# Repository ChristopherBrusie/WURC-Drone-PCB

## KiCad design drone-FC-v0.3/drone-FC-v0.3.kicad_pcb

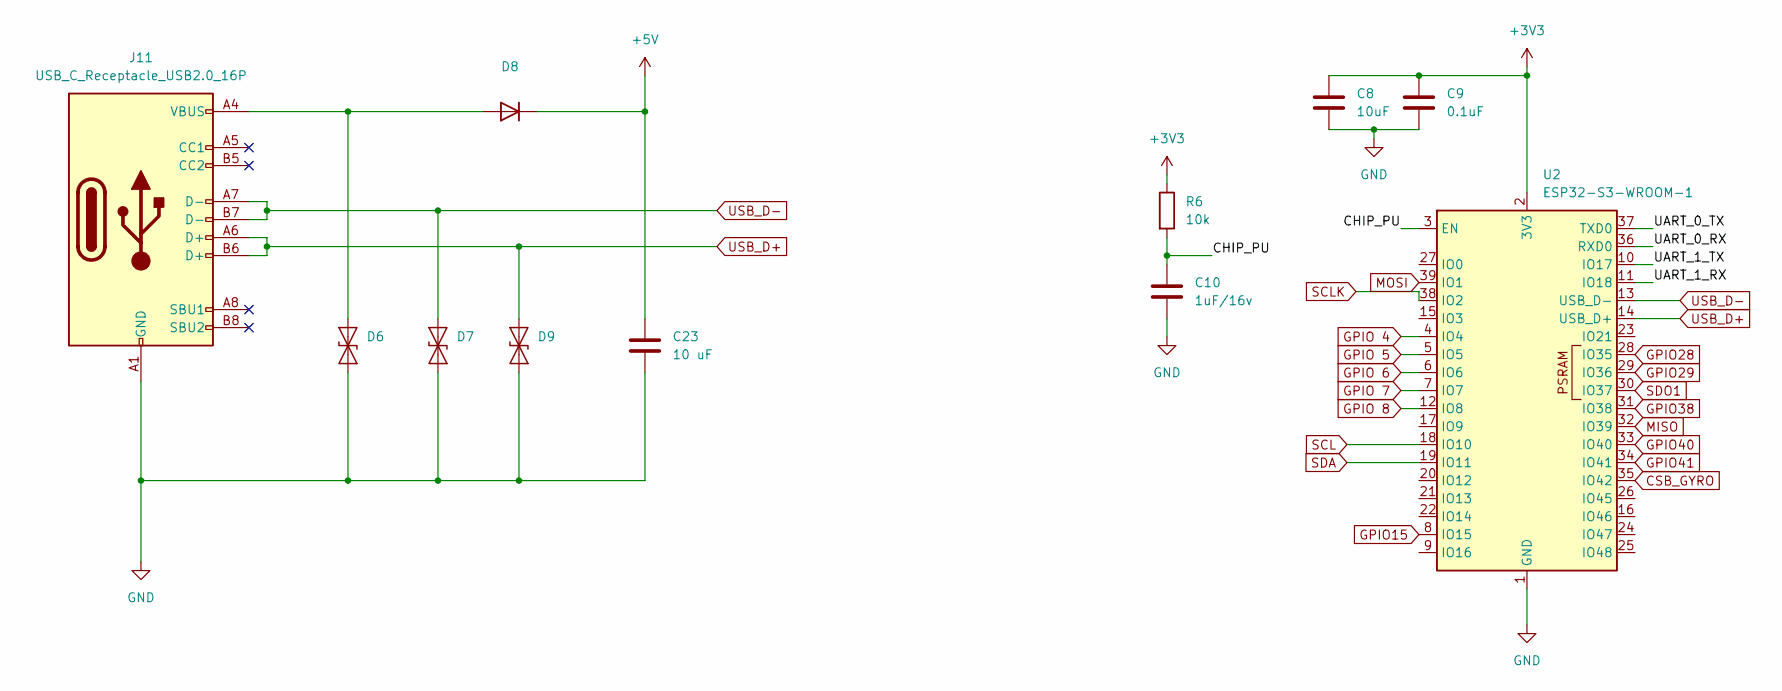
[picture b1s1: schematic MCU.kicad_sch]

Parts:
C8: 10uF; C_0603_1608Metric
C9: 0.1uF; C_0603_1608Metric
C10: 1uF/16v; C_0603_1608Metric
C23: 10 uF; C_0201_0603Metric; LCSC C89632
D6, D7, D9: ESD9B3.3ST5G; D_SOD-923
D8: 1N4148WT; D_SOD-523
J11: USB_C_Receptacle_USB2.0_16P; USB_C_Receptacle_HRO_TYPE-C-31-M-12
R6: 10k; R_0603_1608Metric
U2: ESP32-S3-WROOM-1

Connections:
+3V3: C8.1, C9.1, R6.1, U2.2 (3V3); also elsewhere on the board
+5V: C23.1, D8.1 (K); also elsewhere on the board
/MCU/CHIP_PU: C10.1, R6.2, U2.3 (EN)
/MCU/UART_0_RX: U2.36 (RXD0)
/MCU/UART_0_TX: U2.37 (TXD0)
/MCU/UART_1_RX: U2.11 (IO18)
/MCU/UART_1_TX: U2.10 (IO17)
CSB_GYRO: U2.35 (IO42); also elsewhere on the board
GND: C8.2, C9.2, C10.2, C23.2, D6.1 (A1), D7.1 (A1), D9.1 (A1), J11.A1 (GND), J11.A12 (GND), J11.B1 (GND), J11.B12 (GND), U2.1 (GND), U2.40 (GND), U2.41 (GND); also elsewhere on the board
GPIO15: U2.8 (IO15)
GPIO28: U2.28 (IO35); also elsewhere on the board
GPIO29: U2.29 (IO36); also elsewhere on the board
GPIO38: U2.31 (IO38); also elsewhere on the board
GPIO40: U2.33 (IO40); also elsewhere on the board
GPIO41: U2.34 (IO41); also elsewhere on the board
GPIO 4: U2.4 (IO4); also elsewhere on the board
GPIO 5: U2.5 (IO5); also elsewhere on the board
GPIO 6: U2.6 (IO6); also elsewhere on the board
GPIO 7: U2.7 (IO7); also elsewhere on the board
GPIO 8: U2.12 (IO8); also elsewhere on the board
MISO: U2.32 (IO39); also elsewhere on the board
MOSI: U2.39 (IO1); also elsewhere on the board
unnamed: D6.2 (A2), D8.2 (A), J11.A4 (VBUS), J11.A9 (VBUS), J11.B4 (VBUS), J11.B9 (VBUS)
SCL: U2.18 (IO10); also elsewhere on the board
SCLK: U2.38 (IO2); also elsewhere on the board
SDA: U2.19 (IO11); also elsewhere on the board
SDO1: U2.30 (IO37)
USB_D+: D9.2 (A2), J11.A6 (D+), J11.B6 (D+), U2.14 (USB_D+)
USB_D-: D7.2 (A2), J11.A7 (D-), J11.B7 (D-), U2.13 (USB_D-)

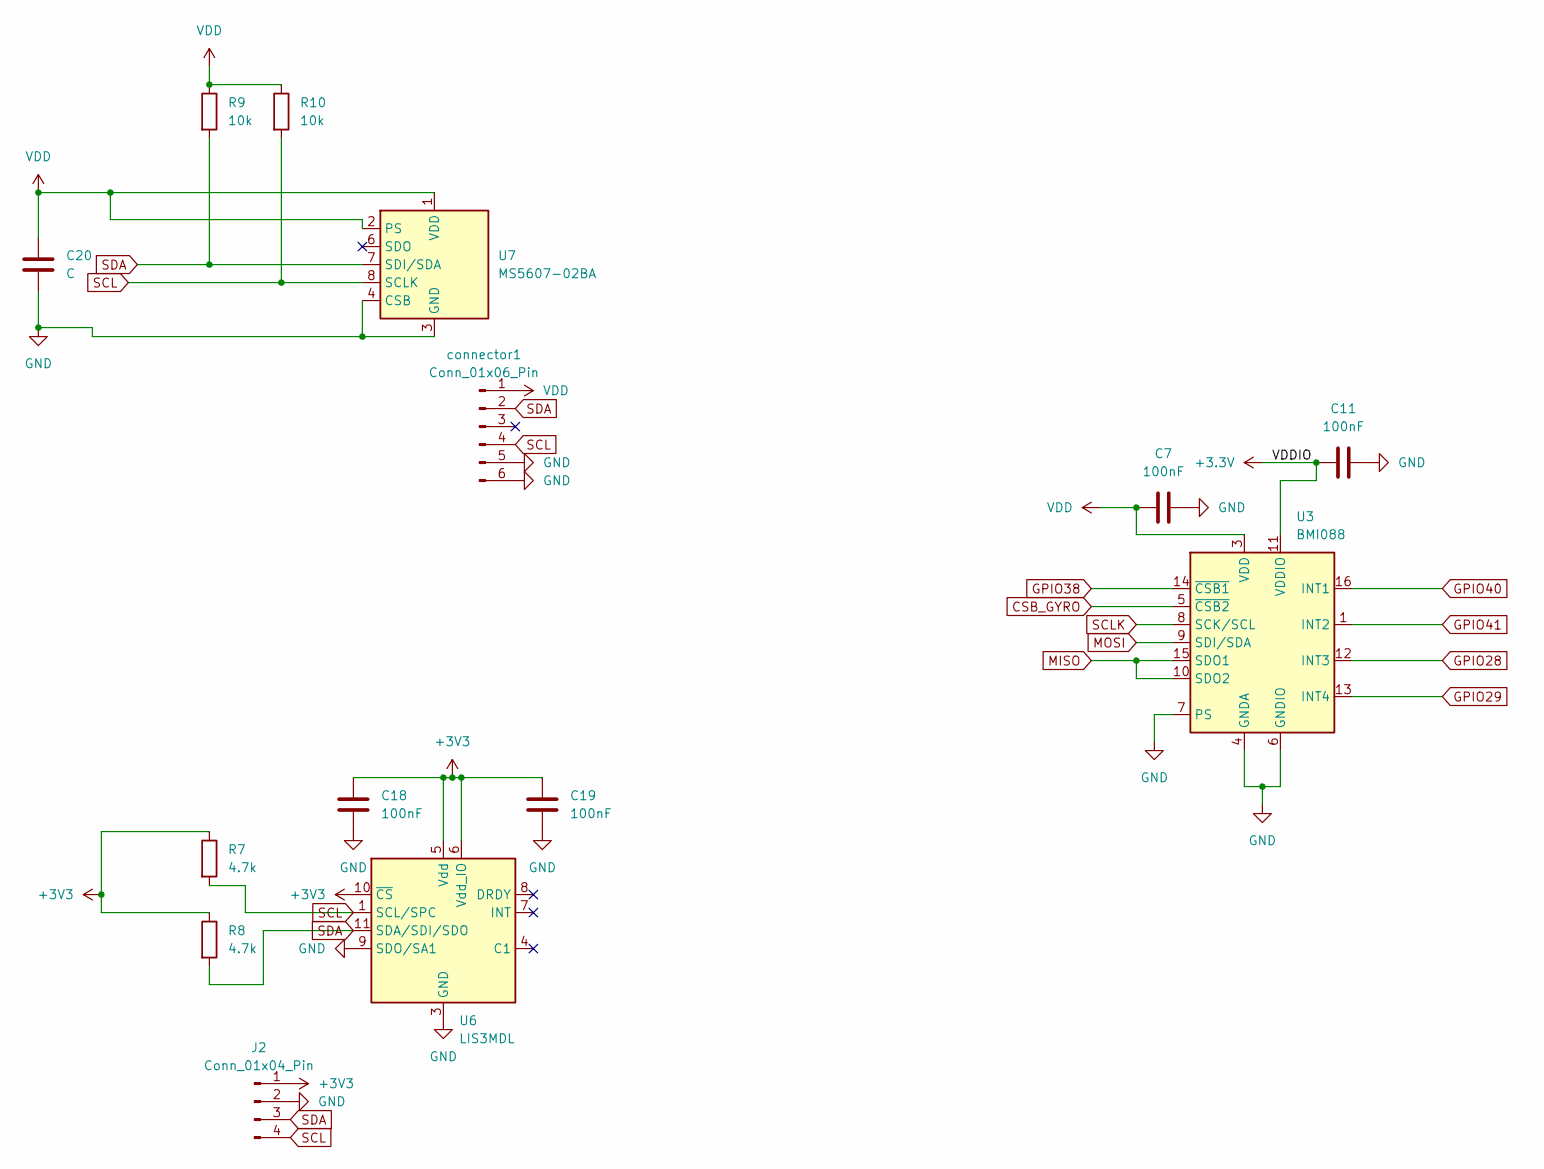
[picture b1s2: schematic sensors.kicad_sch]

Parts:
C7, C11: 100nF; C_0603_1608Metric
C18, C19: 100nF; C_0402_1005Metric
C20: C; C_0201_0603Metric
J2: Conn_01x04_Pin; FanPinHeader_1x04_P2.54mm_Vertical
R7, R8: 4.7k; R_0402_1005Metric
R9, R10: 10k; R_0603_1608Metric_Pad0.98x0.95mm_HandSolder
U3: BMI088; Bosch_LGA-16_4.5x3mm_P0.5mm_LayoutBorder7x1y_ClockwisePinNu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
U6: LIS3MDL; LGA-12_2x2mm_P0.5mm
U7: MS5607-02BA; LGA-8_3x5mm_P1.25mm; lcsc C97627
connector1: Conn_01x06_Pin; PinHeader_1x06_P2.54mm_Vertical

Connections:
+3.3V: C11.1, U3.11 (VDDIO); also elsewhere on the board
+3V3: C18.1, C19.1, J2.1, R7.1, R8.1, U6.5 (Vdd), U6.6 (Vdd_IO), U6.10 (~CS); also elsewhere on the board
CSB_GYRO: U3.5 (~CSB2); also elsewhere on the board
GND: C7.2, C11.2, C18.2, C19.2, C20.2, J2.2, U3.2 (GNDA), U3.4 (GNDA), U3.6 (GNDIO), U3.7 (PS), U6.2 (GND), U6.3 (GND), U6.9 (SDO/SA1), U6.12 (GND), U7.3 (GND), U7.4 (CSB), U7.5 (CSB), connector1.5, connector1.6; also elsewhere on the board
GPIO28: U3.12 (INT3); also elsewhere on the board
GPIO29: U3.13 (INT4); also elsewhere on the board
GPIO38: U3.14 (~CSB1); also elsewhere on the board
GPIO40: U3.16 (INT1); also elsewhere on the board
GPIO41: U3.1 (INT2); also elsewhere on the board
MISO: U3.10 (SDO2), U3.15 (SDO1); also elsewhere on the board
MOSI: U3.9 (SDI/SDA); also elsewhere on the board
SCL: J2.4, R7.2, R10.2, U6.1 (SCL/SPC), U7.8 (SCLK), connector1.4; also elsewhere on the board
SCLK: U3.8 (SCK/SCL); also elsewhere on the board
SDA: J2.3, R8.2, R9.2, U6.11 (SDA/SDI/SDO), U7.7 (SDI/SDA), connector1.2; also elsewhere on the board
VDD: C7.1, C20.1, R9.1, R10.1, U3.3 (VDD), U7.1 (VDD), U7.2 (PS), connector1.1

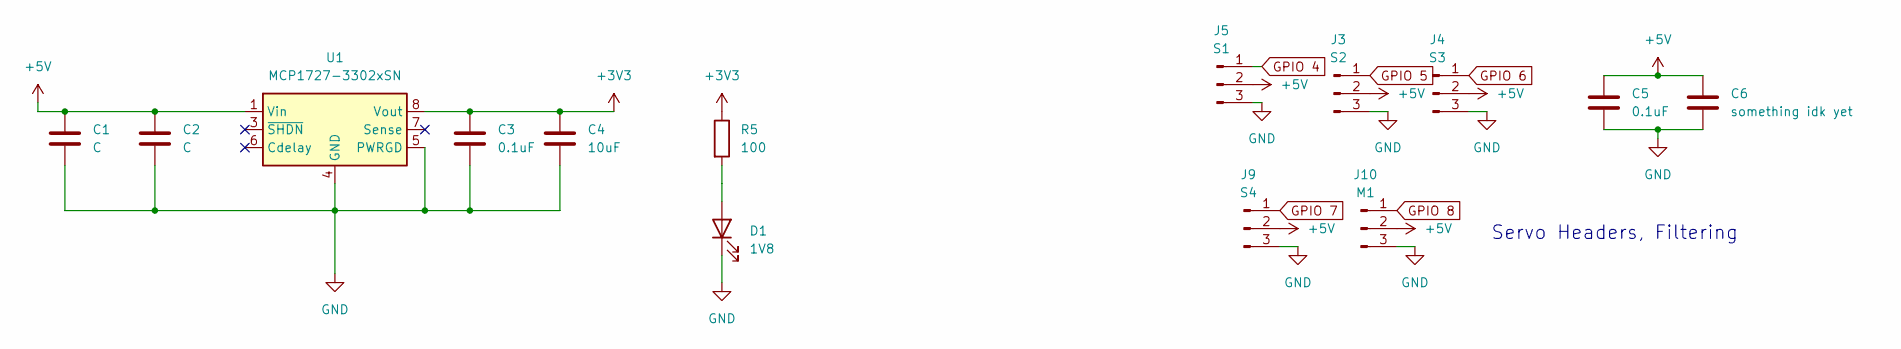
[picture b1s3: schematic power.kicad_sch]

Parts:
C1, C2: C; C_0603_1608Metric
C3: 0.1uF; C_0603_1608Metric
C4: 10uF; C_0603_1608Metric; LCSC C1691
C5: 0.1uF; C_0603_1608Metric; LCSC C91183
C6: something idk yet; C_Radial_D6.3mm_H5.0mm_P2.50mm
D1: 1V8; LED_0603_1608Metric; LCSC C12065
J3: S2; PinHeader_1x03_P2.54mm_Vertical
J4: S3; PinHeader_1x03_P2.54mm_Vertical
J5: S1; PinHeader_1x03_P2.54mm_Vertical
J9: S4; PinHeader_1x03_P2.54mm_Vertical
J10: M1; PinHeader_1x03_P2.54mm_Vertical
R5: 100; R_0603_1608Metric; LCSC C177347
U1: MCP1727-3302xSN; SOIC-8_3.9x4.9mm_P1.27mm

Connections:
+3V3: C3.1, C4.1, R5.1, U1.8 (Vout); also elsewhere on the board
+5V: C1.1, C2.1, C5.1, C6.1, J3.2, J4.2, J5.2, J9.2, J10.2, U1.1 (Vin), U1.2 (Vin); also elsewhere on the board
GND: C1.2, C2.2, C3.2, C4.2, C5.2, C6.2, D1.1 (K), J3.3, J4.3, J5.3, J9.3, J10.3, U1.4 (GND), U1.5 (PWRGD); also elsewhere on the board
GPIO 4: J5.1; also elsewhere on the board
GPIO 5: J3.1; also elsewhere on the board
GPIO 6: J4.1; also elsewhere on the board
GPIO 7: J9.1; also elsewhere on the board
GPIO 8: J10.1; also elsewhere on the board
unnamed: D1.2 (A), R5.2

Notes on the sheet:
Servo Headers, Filtering

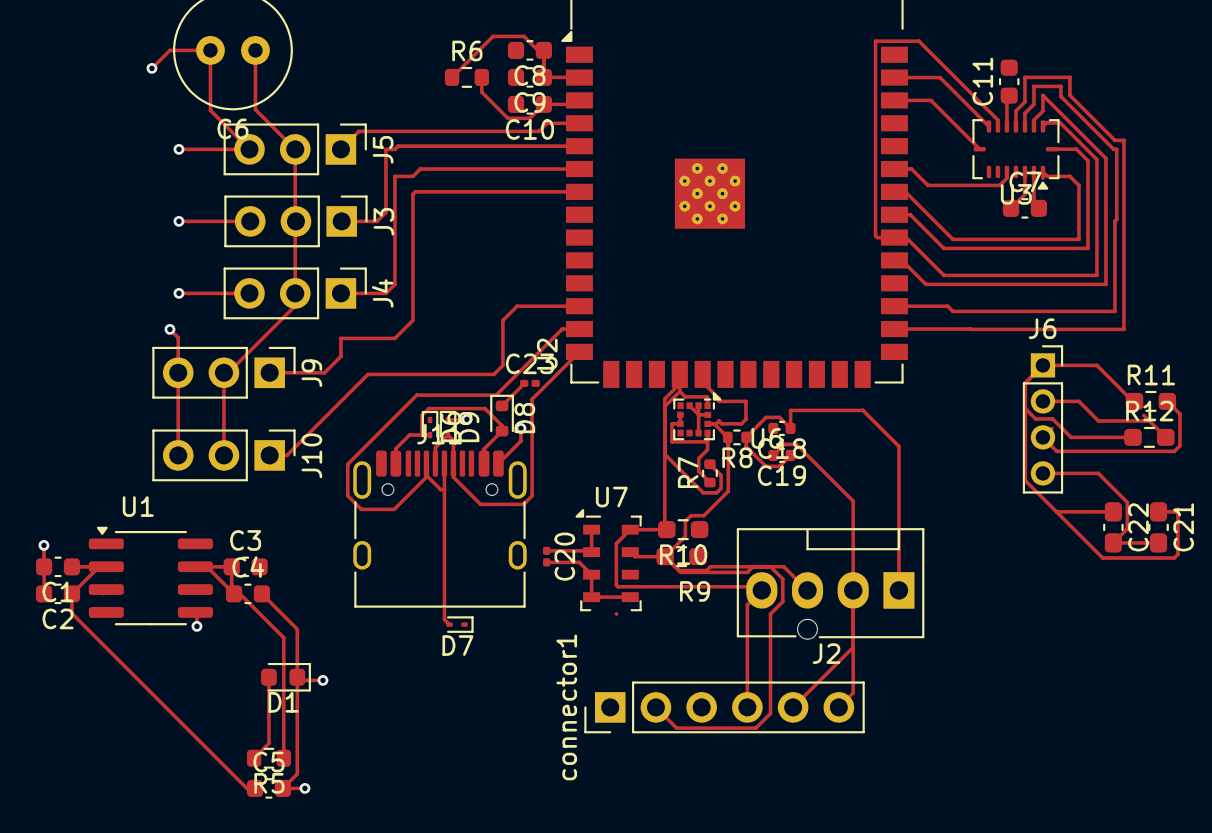
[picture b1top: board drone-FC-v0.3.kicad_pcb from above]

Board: 2 copper layers, 44 parts (0 on the bottom side), 28 nets.

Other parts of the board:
C21: 100nF; C_0603_1608Metric_Pad1.08x0.95mm_HandSolder
C22: C; C_0603_1608Metric_Pad1.08x0.95mm_HandSolder
J6: Conn_01x04_Pin; PinSocket_1x04_P2.00mm_Vertical
R11, R12: 10kohm; R_0603_1608Metric_Pad0.98x0.95mm_HandSolder

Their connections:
+3.3V: C21.1, C22.1, J6.1, R11.1, R12.1; also elsewhere on the board
/Sensors/SCL: J6.2, R12.2
/Sensors/SDA: J6.3, R11.2
GND: C21.2, C22.2, J6.4; also elsewhere on the board

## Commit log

2026-02-15 init
2026-02-15 sheets
2026-03-21 what
2026-03-21 added magnetic sensor and pressure sensor
2026-03-21 added USBC and IMU sensor
2026-03-24 whatever
2026-03-28 added sensor connections
2026-03-31 added bmi088
2026-04-01 modified the schematics to three sensors and added some of the PCB layouts
2026-04-04 fixed usb footprint issue
2026-04-04 "Added Global Labels + deleted unnecessary parts on the PCB"
2026-04-07 "global labels added"
    "global labels added"
2026-04-08 added global labels for BMI088
2026-04-08 connected U3 to U2
2026-04-11 changed sda and scl labels
2026-04-11 added sda and scl labels
2026-04-22 "Unfinished PCB connections"
2026-04-25 added connections and ground plane
